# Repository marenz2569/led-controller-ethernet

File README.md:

# led-controller-ethernet

led-controller-ethernet is the hardware to the [avr-ethernet-licht firmware](https://github.com/marenz2569/avr-ethernet-licht).

Its purpurse is to control ws2812 protocol compatible leds via a [udp protocol](https://chch.it/Fensterbogenbeleuchtung).

In addition to the pcb the hardware uses an arduino pro mini and an enc28j60 breakout board.

## flexibilty

input voltage | output voltage | bridges | notes
--- | --- | --- | ---
12-36V | 12-36V | JP1 |
12-36V | 5V | JP2 |
5V | 5V | JP1 and JP2 | do not populate voltage regulator

## todo
- test if regulator may be populated when inserting 5 Volts to V\_in and bridging JP1 and JP2
- add option for rgb leds with 3 mosfets.

## license
see lgplv2.1 in LICENSE file.

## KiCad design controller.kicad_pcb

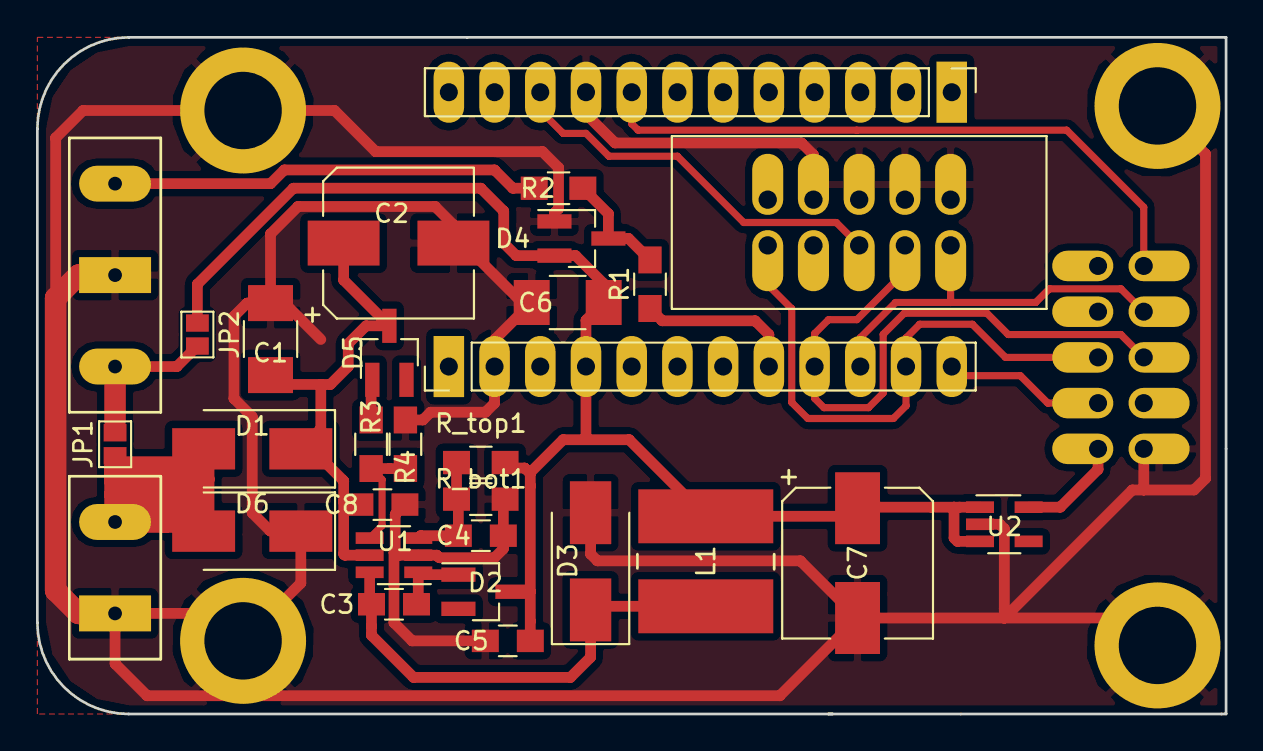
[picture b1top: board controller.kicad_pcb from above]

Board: 2 copper layers, 66.0 x 37.6 mm, 35 parts (1 on the bottom side), 20 nets.

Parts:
C1, C6: 10u; C_1210_HandSoldering
C2: 100u; CP_Elec_8x10
C3, C5, C8: 100n; C_0805_HandSoldering
C4: n.b.; C_0805_HandSoldering
C7: 470u; CP_Elec_8x10
CON1: AVR-ISP-10; IDC_Header_Straight_10pins
D1, D3: SS24/SS26; D_SMB_Handsoldering
D2: BAS70-06; SOT-23_Handsoldering
D4: BAV99; SOT-23_Handsoldering
D5: BZX84C 8V2; D_SOT-23_ANK
D6: P6SMB36CA; D_SMB_Handsoldering
JP1: JUMPER; GS2
JP2: JUMPER_NO_Small; GS2
L1: 33u; Choke_SMD_Wuerth-WE-PD2-Typ-L
P1: VIN; 2_5.08mm
P2: LEDOUT; 3_5.08mm
P3, P5: CONN_01X12; Socket_Strip_Straight_1x12_Pitch2.54mm
P4: CONN_02X05; Socket_Strip_Straight_2x05_Pitch2.54mm
P6, P7, P8, P9: CONN_01X01; MountingHole_4.3mm_M4_ISO14580_Pad
R1, R2: 50R; R_0805_HandSoldering
R3, R4: 10k; R_0805_HandSoldering
R_bot1: 8k2; R_0805_HandSoldering
R_top1: 43k; R_0805_HandSoldering
U1: MCP16331; SOT-23-6_Handsoldering
U2: TLV70033DDC; SOT-23-5_HandSoldering

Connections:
+3V3: P4.9, U2.5
+5V: C5.1, C6.1, C7.1, D2.3, D4.2, JP2.1, L1.1, P5.4, R_top1.1, U2.1, U2.3
GND: C1.2, C2.2, C4.2, C5.2, C6.2, C7.2, C8.2, CON1.4, CON1.6, CON1.8, CON1.10, D3.2, D4.1, D6.1, P1.2, P2.2, P3.9, P4.10, P5.2, P6.1, P7.1, P8.1, P9.1, R4.2, R_bot1.2, U1.2, U2.2
INT0: P3.8, P4.2
LEDOUT: P2.1, R2.1
MISO: CON1.9, P4.4, P5.10
MOSI: CON1.1, P4.5, P5.11
unnamed: C1.1, C2.1, C8.1, D1.1, D5.1, U1.5
unnamed: C3.1, D2.1, U1.1
unnamed: C3.2, D3.1, L1.2, U1.6
unnamed: C4.1, R_bot1.1, R_top1.2, U1.3
unnamed: D4.3, R1.2, R2.2
unnamed: D5.2, R3.2
unnamed: R3.1, R4.1, U1.4
OUT: JP1.2, JP2.2, P2.3
PORTC0: P5.8, R1.1
RS: CON1.5, P3.10, P5.3
SCK: CON1.7, P4.6, P5.9
SS: P4.7, P5.12
VIN: D1.2, D6.2, JP1.1, P1.1

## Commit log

2017-07-23 gitignore for kicad project
2017-07-23 added readme
2017-07-23 added hardware version 1.3-2
2017-07-23 Create LICENSE
2017-07-23 Update LICENSE
2017-07-23 V_in starts at 12 Volts
2017-07-23 flexibilty is now described in a nice table
2020-08-30 changed some things, years ago
2020-08-30 added solvespace files for case of controller
